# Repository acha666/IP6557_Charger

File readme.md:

# IP6557 Charger

[Chinese Document / 中文文档](./readme-zh.md) | English Document

*A fast-charging module based on the Injoinic IP6557 buck-boost SoC*  

## Project Status

- [x] Schematic design  
- [x] PCB layout  
- [x] PCB fabrication  
- [x] PCB validation  

## Device Overview

- **[IP6557-C]()** – An SoC that integrates a buck-boost controller and USB-C fast-charging protocols  
- **[NTTFS5C673NL](https://www.onsemi.com/download/data-sheet/pdf/nttfs5c673nl-d.pdf) MOSFET** –  
  $`V_{DS}=60\,\text{V},\;R_{DS(\mathrm{on})}=11\,\text{m}\Omega,\;C_{\mathrm{iss}}=880\,\text{pF},\;Q_{g(\mathrm{th})}=1.0\,\text{nC}\;@\,4.5\,\text{V}`$

## Key PCB Parameters

| Parameter | Value |
|:---:|:---:|
| **Dimensions** | 38.50 mm × 14.70 mm |
| **Board shape** | Rounded rectangle, r = 0.50 mm |
| **Finished thickness** | 1.00 mm |
| **Copper layers** | 4 |
| **Min. trace width** | 0.12 mm |
| **Min. trace spacing** | 0.12 mm |
| **Min. plated hole Ø** | 0.20 mm |
| **Min. non-plated hole Ø** | 0.65 mm |
| **Min. via outer Ø** | 0.45 mm |
| **Min. via inner Ø** | 0.20 mm |
| **Min. plated slot width** | 0.60 mm |
| **Min. non-plated slot width** | N/A |

## Project Description

This project was designed with KiCad 9.0.2.

A GitHub Actions CI/CD workflow runs DRC checks and generates manufacturing files (Gerber, etc.) automatically on every commit.

Manufacturing files are available from the [Release page](https://github.com/acha666/IP6557_Charger/releases) or the [Workflow page](https://github.com/acha666/IP6557_Charger/actions/workflows/kicad-ci.yml).

### Notes

*(This document was translated by ChatGPT.)*

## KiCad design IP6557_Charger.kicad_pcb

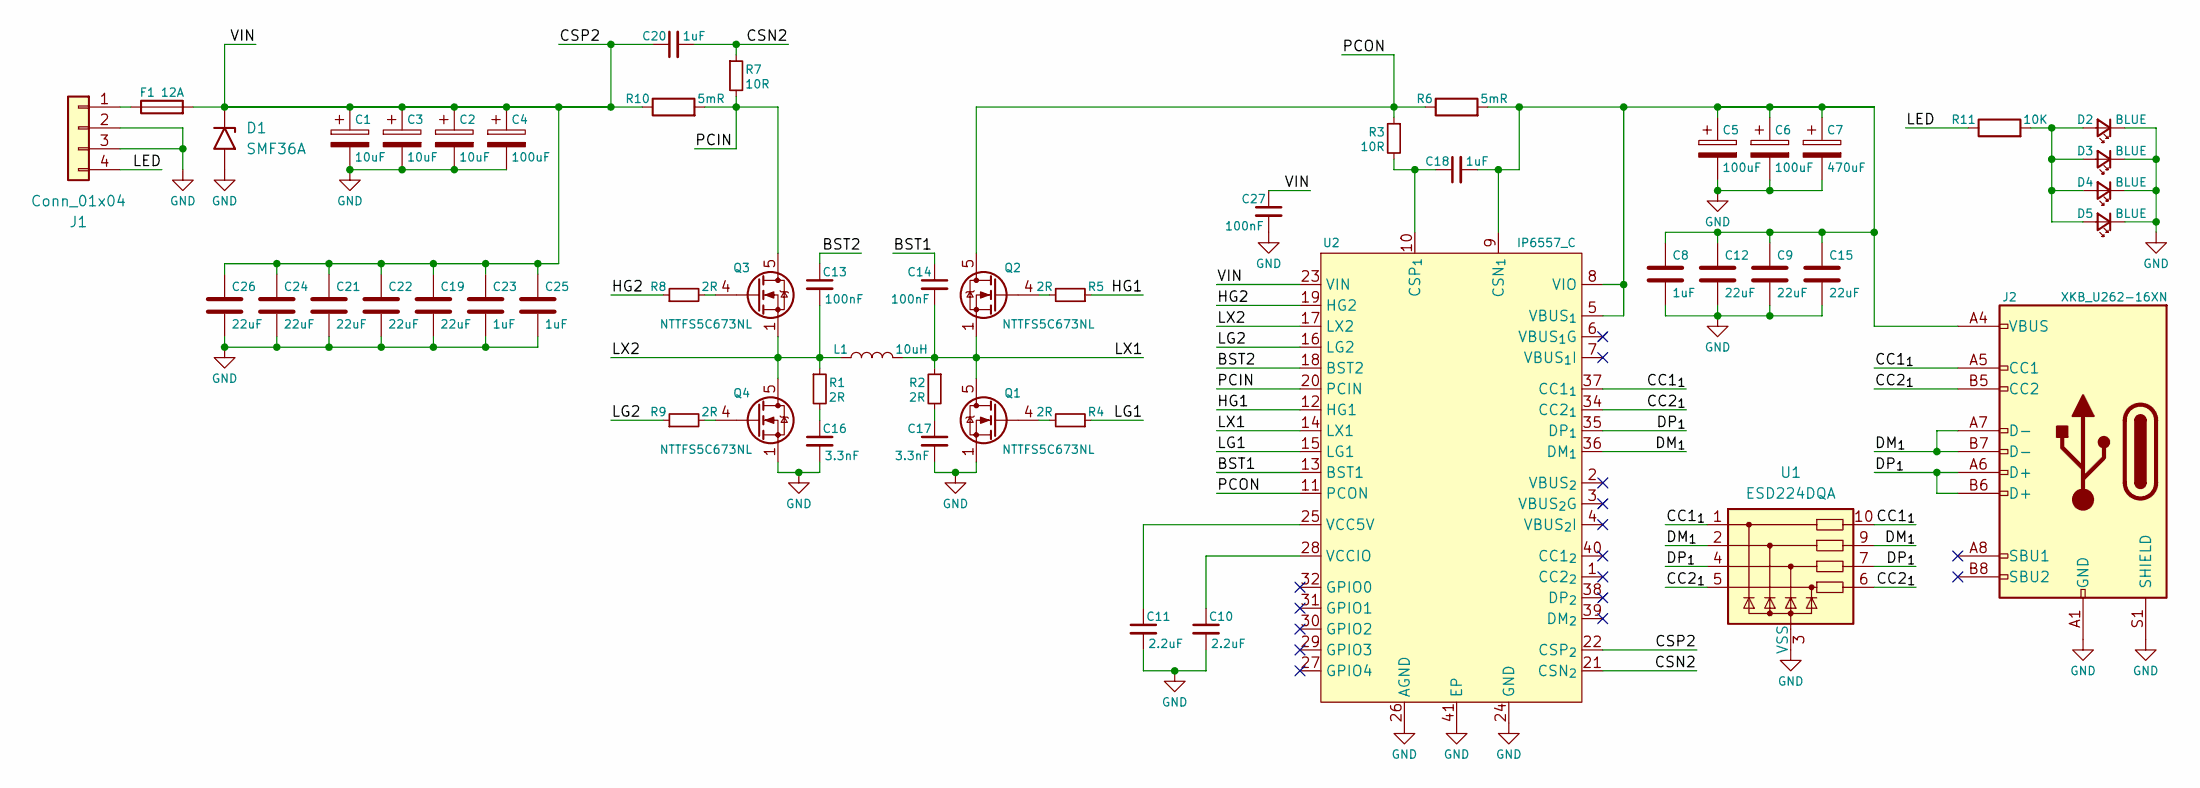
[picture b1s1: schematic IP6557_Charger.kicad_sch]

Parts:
C1, C2, C3: 10uF; CP_Radial_D4.0mm_P1.50mm
C4: 100uF; CP_Radial_D5.0mm_P2.00mm
C5, C6: 100uF; CP_Radial_D6.3mm_P2.50mm
C7: 470uF; CP_Radial_D8.0mm_P3.50mm
C8: 1uF; C_0805_2012Metric
C9, C12, C15: 22uF; C_1206_3216Metric
C10, C11: 2.2uF; C_0402_1005Metric
C13, C14, C27: 100nF; C_0402_1005Metric
C16, C17: 3.3nF; C_0402_1005Metric
C18, C20: 1uF; C_0402_1005Metric
C19, C21, C22, C24, C26: 22uF; C_0805_2012Metric
C23, C25: 1uF; C_0603_1608Metric
D1: SMF36A; D_SMF
D2, D3, D4, D5: BLUE; LED_0402_1005Metric
F1: 12A; Fuse_1206_3216Metric
J1: Conn_01x04; PinHeader_1x04_P2.54mm_Horizontal
J2: XKB_U262-16XN; USB_C_Receptacle_XKB_U262-16XN-4BVC11
L1: 10uH; L_Changjiang_FEXL0880A
Q1, Q2, Q3, Q4: NTTFS5C673NL; VSON-8_3.3x3.3mm_P0.65mm_NexFET
R1, R2, R4, R5, R8, R9: 2R; R_0402_1005Metric
R3, R7: 10R; R_0402_1005Metric
R6, R10: 5mR; R_0805_2012Metric
R11: 10K; R_0805_2012Metric
U1: ESD224DQA; Diodes_UDFN-10_1.0x2.5mm_P0.5mm
U2: IP6557_C; VQFN-40-1EP_5x5mm_P0.4mm_EP3.6x3.6mm_ThermalVias

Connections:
/BST1: C14.1, U2.13 (BST1)
/BST2: C13.1, U2.18 (BST2)
/CC1_{1}: J2.A5 (CC1), U1.1, U1.10, U2.37 (CC1_{1})
/CC2_{1}: J2.B5 (CC2), U1.5, U1.6, U2.34 (CC2_{1})
/CSN2: C20.2, R7.1, U2.21 (CSN_{2})
/CSP2: C1.1, C2.1, C3.1, C4.1, C19.1, C20.1, C21.1, C22.1, C23.1, C24.1, C25.1, C26.1, C27.1, D1.1 (A1), F1.2, R10.1, U2.22 (CSP_{2}), U2.23 (VIN)
/DM_{1}: J2.A7 (D-), J2.B7 (D-), U1.2, U1.9, U2.36 (DM_{1})
/DP_{1}: J2.A6 (D+), J2.B6 (D+), U1.4, U1.7, U2.35 (DP_{1})
/HG1: R5.1, U2.12 (HG1)
/HG2: R8.1, U2.19 (HG2)
/LED: J1.4, R11.1
/LG1: R4.1, U2.15 (LG1)
/LG2: R9.1, U2.16 (LG2)
/LX1: C14.2, L1.2, Q1.5 (D), Q2.1 (S), Q2.2 (S), Q2.3 (S), R2.1, U2.14 (LX1)
/LX2: C13.2, L1.1, Q3.1 (S), Q3.2 (S), Q3.3 (S), Q4.5 (D), R1.1, U2.17 (LX2)
/PCIN: Q3.5 (D), R7.2, R10.2, U2.20 (PCIN)
/PCON: Q2.5 (D), R3.1, R6.1, U2.11 (PCON)
GND: C1.2, C2.2, C3.2, C4.2, C5.2, C6.2, C7.2, C8.2, C9.2, C10.2, C11.2, C12.2, C15.2, C16.2, C17.2, C19.2, C21.2, C22.2, C23.2, C24.2, C25.2, C26.2, C27.2, D1.2 (A2), D2.1 (K), D3.1 (K), D4.1 (K), D5.1 (K), J1.2, J1.3, J2.A1 (GND), J2.A12 (GND), J2.B1 (GND), J2.B12 (GND), J2.S1 (SHIELD), Q1.1 (S), Q1.2 (S), Q1.3 (S), Q4.1 (S), Q4.2 (S), Q4.3 (S), U1.3 (VSS), U1.8 (VSS), U2.24 (GND), U2.26 (AGND), U2.41 (EP)
unnamed: C16.1, R1.2
unnamed: C17.1, R2.2
unnamed: D2.2 (A), D3.2 (A), D4.2 (A), D5.2 (A), R11.2
unnamed: F1.1, J1.1
unnamed: Q1.4 (G), R4.2
unnamed: Q2.4 (G), R5.2
unnamed: Q3.4 (G), R8.2
unnamed: Q4.4 (G), R9.2
unnamed: C5.1, C6.1, C7.1, C8.1, C9.1, C12.1, C15.1, C18.2, J2.A4 (VBUS), J2.A9 (VBUS), J2.B4 (VBUS), J2.B9 (VBUS), R6.2, U2.5 (VBUS_{1}), U2.8 (VIO), U2.9 (CSN_{1})
unnamed: C18.1, R3.2, U2.10 (CSP_{1})
unnamed: C11.1, U2.25 (VCC5V)
unnamed: C10.1, U2.28 (VCCIO)

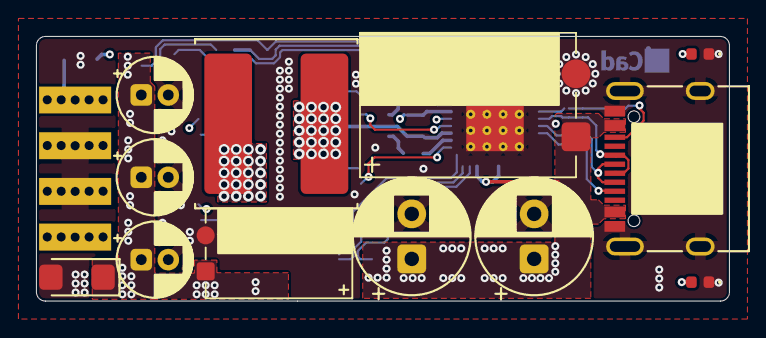
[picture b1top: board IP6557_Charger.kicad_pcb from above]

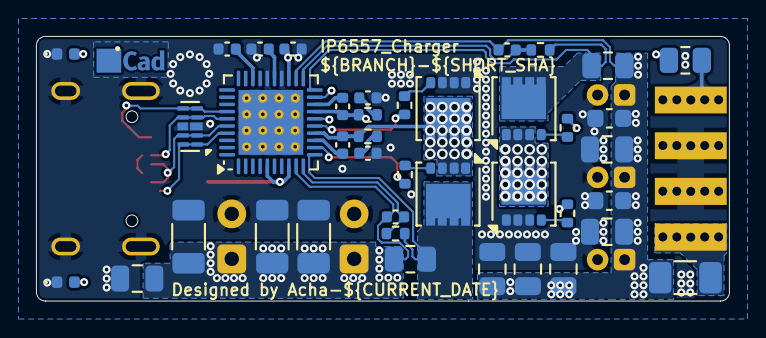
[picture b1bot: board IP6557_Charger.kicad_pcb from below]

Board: 4 copper layers, 38.5 x 14.7 mm, 53 parts (40 on the bottom side), 30 nets.
